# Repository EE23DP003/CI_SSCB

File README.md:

# CI_SSCB
This repository contains design files for two different coupled inductor based Solid-State Circuit Breakers (SSCBs)

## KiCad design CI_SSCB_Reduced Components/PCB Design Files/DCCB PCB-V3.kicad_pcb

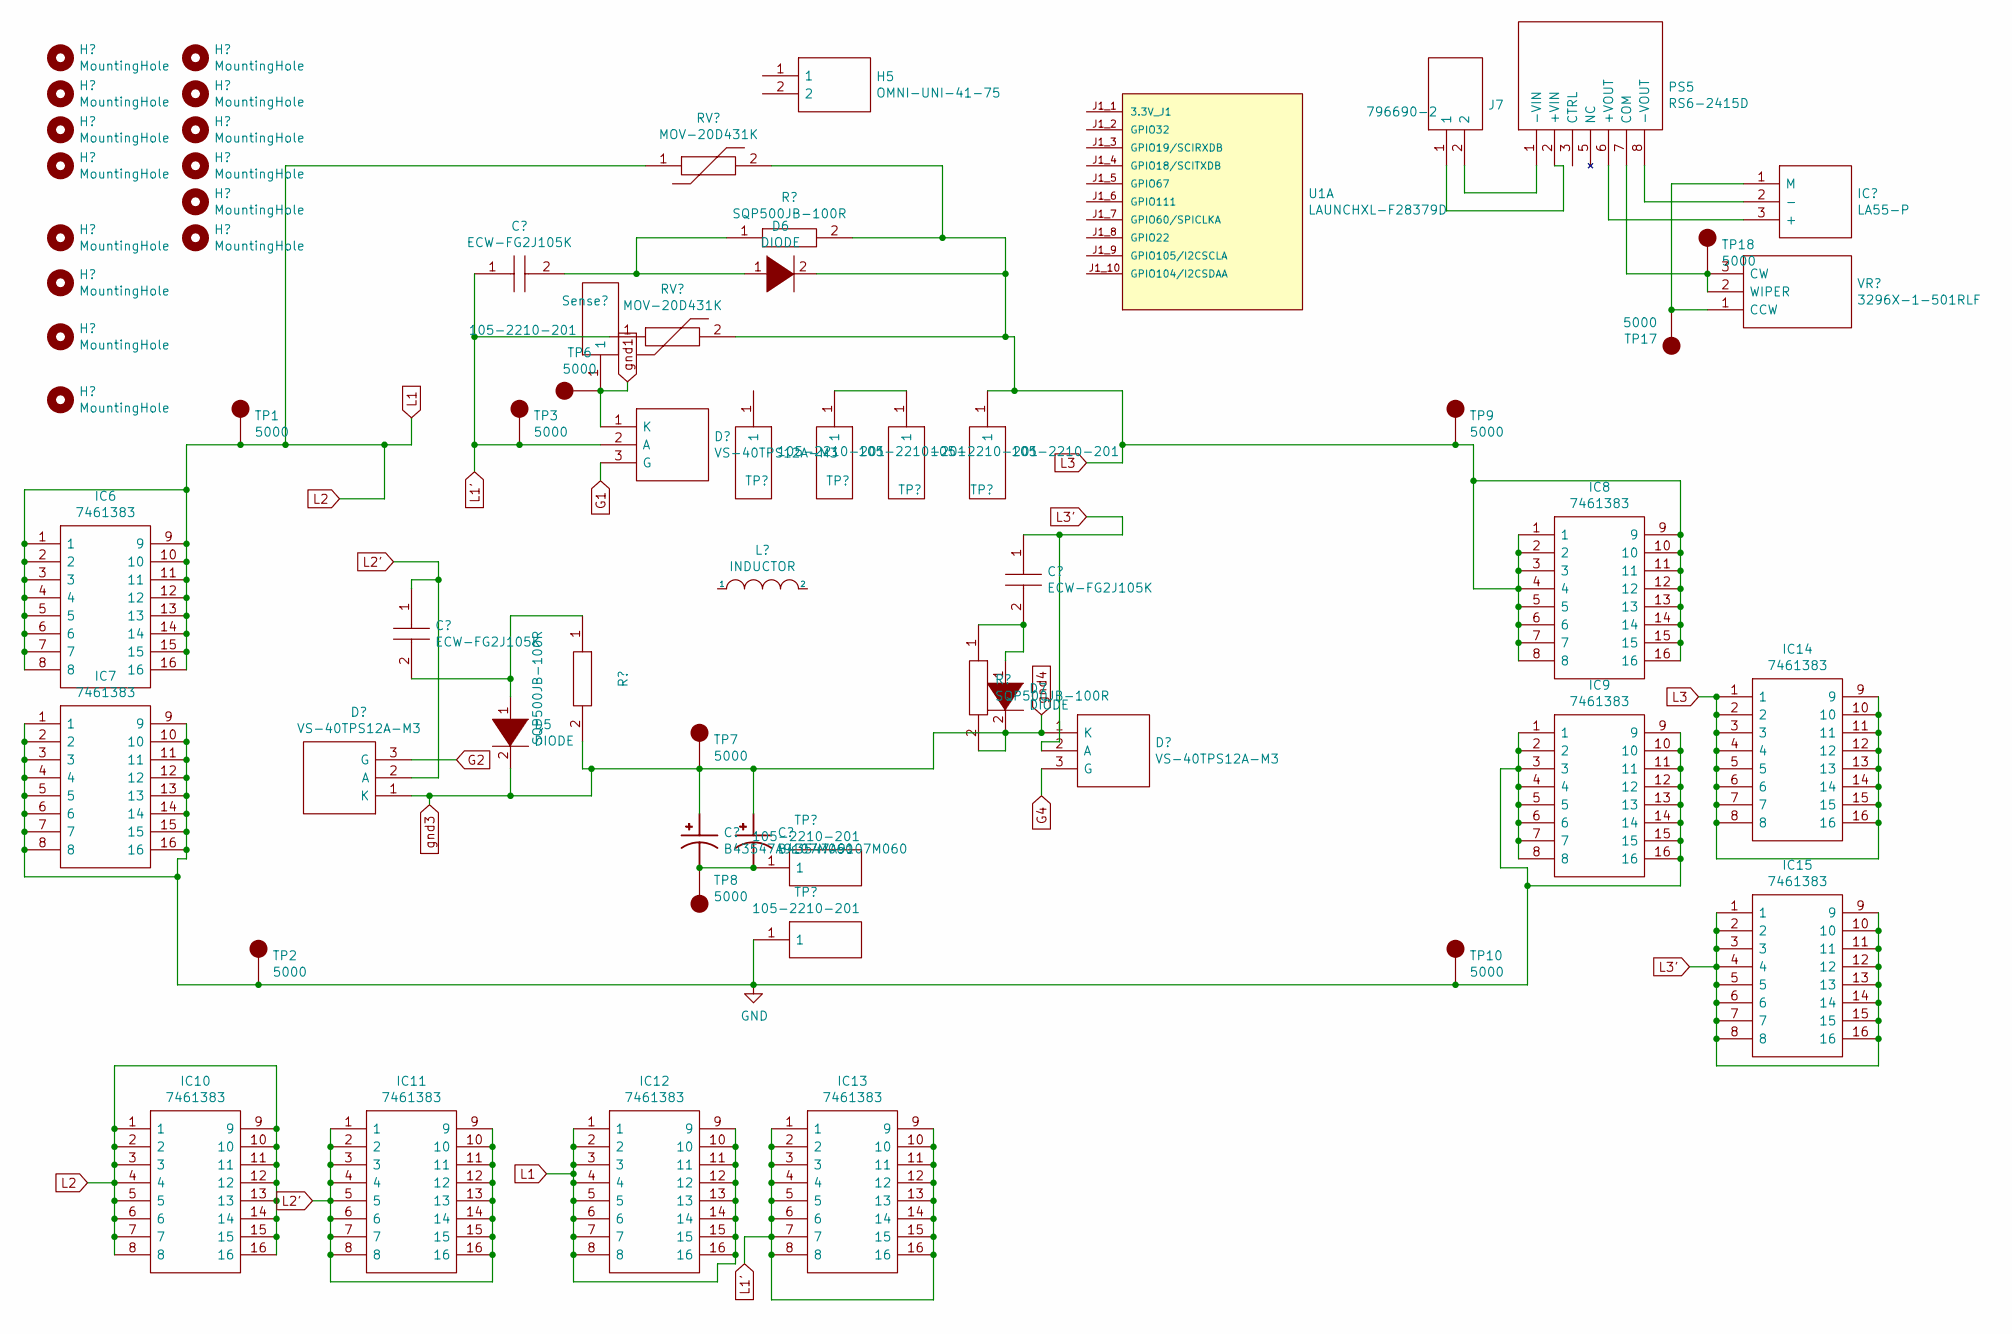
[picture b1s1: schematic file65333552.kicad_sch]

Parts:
C1, C2, C4: ECW-FG2J105K; ECWFG2J105K; Manufacturer_Part_Number ECW-FG2J105K
C3, C11: B43547A9107M060; CAPPRD1000W190D2550H2700; PARTREV 2018-10
D1, D2, D3: VS-40TPS12A-M3; TO546P531X1558X2499-3P; Manufacturer_Part_Number VS-40TPS12A-M3; Mouser Part Number 844-40TPS12A-M3
D5, D6, D7: DIODE; D_P600_R-6_P12.70mm_Horizontal
H1, H2, H3, H4, H6, H7, H8, H9, H10, H11, H12, H13, H14, H15: MountingHole; MountingHole_3.2mm_M3
H5: OMNI-UNI-41-75; OMNIUNI4175; Mouser Part Number 567-OMNI-UNI-41-75
IC1: LA55-P; LA55P; Manufacturer_Part_Number LA55-P
IC6, IC7, IC8, IC9, IC10, IC11, IC12, IC13, IC14, IC15: 7461383; Manufacturer_Part_Number 7461383
J7: 796690-2; SHDR2W101P0X500_1X2_1000X1250X1500P; Manufacturer_Part_Number 796690-2; Mouser Part Number 571-796690-2
K1: 105-2210-201; 1052210201; Mouser Part Number 530-105-2210-1
L1: INDUCTOR; EE422120_bobbin_diff_modified
PS5: RS6-2415D; RS60505S; Manufacturer_Part_Number RS6-2415D; Mouser Part Number 919-RS6-2415D
Probe1, Probe2: 105-2210-201; 1052210201; Mouser Part Number 530-105-2210-1
R1, R2, R3: SQP500JB-100R; RESAD6000W85L2200D950; Manufacturer_Part_Number SQP500JB-100R; Mouser Part Number 603-SQP500JB-100R
RV1, RV2: MOV-20D431K; MOV20D431K; Manufacturer_Part_Number MOV-20D431K; Mouser Part Number 652-MOV-20D431K
Sense1, Sense2: 105-2210-201; 1052210201; Mouser Part Number 530-105-2210-1
TP1, TP2, TP3, TP6, TP7, TP8, TP9, TP10, TP17, TP18: 5000; KEYSTONE_5000
TP4, TP5: 105-2210-201; 1052210201; Mouser Part Number 530-105-2210-1
U1: LAUNCHXL-F28379D; MOD_LAUNCHXL-F28379D; PARTREV 2.0
VR1: 3296X-1-501RLF; 3296X1223LF; Manufacturer_Part_Number 3296X-1-501RLF; Mouser Part Number 652-3296X-1-501RLF

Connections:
G1: D2.3 (G); also elsewhere on the board
G2: D1.3 (G); also elsewhere on the board
G4: D3.3 (G); also elsewhere on the board
GND: IC7.1, IC7.2, IC7.3, IC7.4, IC7.5, IC7.6, IC7.7, IC7.8, IC7.9, IC7.10, IC7.11, IC7.12, IC7.13, IC7.14, IC7.15, IC7.16, IC9.1, IC9.2, IC9.3, IC9.4, IC9.5, IC9.6, IC9.7, IC9.8, IC9.9, IC9.10, IC9.11, IC9.12, IC9.13, IC9.14, IC9.15, IC9.16, TP2.TP, TP5.1, TP10.TP
L1: IC6.1, IC6.2, IC6.3, IC6.4, IC6.5, IC6.6, IC6.7, IC6.8, IC6.9, IC6.10, IC6.11, IC6.12, IC6.13, IC6.14, IC6.15, IC6.16, IC10.1, IC10.2, IC10.3, IC10.4, IC10.5, IC10.6, IC10.7, IC10.8, IC10.9, IC10.10, IC10.11, IC10.12, IC10.13, IC10.14, IC10.15, IC10.16, IC12.1, IC12.2, IC12.3, IC12.4, IC12.5, IC12.6, IC12.7, IC12.8, IC12.9, IC12.10, IC12.11, IC12.12, IC12.13, IC12.14, IC12.15, IC12.16, RV2.1, TP1.TP
L1': C2.1, D2.2 (A), IC13.1, IC13.2, IC13.3, IC13.4, IC13.5, IC13.6, IC13.7, IC13.8, IC13.9, IC13.10, IC13.11, IC13.12, IC13.13, IC13.14, IC13.15, IC13.16, RV1.1, TP3.TP
L2': C1.1, D1.2 (A), IC11.1, IC11.2, IC11.3, IC11.4, IC11.5, IC11.6, IC11.7, IC11.8, IC11.9, IC11.10, IC11.11, IC11.12, IC11.13, IC11.14, IC11.15, IC11.16
L3: D6.2 (A), IC8.1, IC8.2, IC8.3, IC8.4, IC8.5, IC8.6, IC8.7, IC8.8, IC8.9, IC8.10, IC8.11, IC8.12, IC8.13, IC8.14, IC8.15, IC8.16, IC14.1, IC14.2, IC14.3, IC14.4, IC14.5, IC14.6, IC14.7, IC14.8, IC14.9, IC14.10, IC14.11, IC14.12, IC14.13, IC14.14, IC14.15, IC14.16, Probe2.1, R2.2, RV1.2, RV2.2, TP9.TP
L3': C4.1, D3.2 (A), IC15.1, IC15.2, IC15.3, IC15.4, IC15.5, IC15.6, IC15.7, IC15.8, IC15.9, IC15.10, IC15.11, IC15.12, IC15.13, IC15.14, IC15.15, IC15.16
unnamed: C1.2, D5.1 (K), R1.1
unnamed: C2.2, D6.1 (K), R2.1
unnamed: C4.2, D7.1 (K), R3.1
unnamed: C3.2, C11.2, TP4.1, TP8.TP
unnamed: IC1.1 (M), TP17.TP, VR1.1 (CCW)
unnamed: IC1.2 (-), PS5.8 (-VOUT)
unnamed: IC1.3 (+), PS5.6 (+VOUT)
unnamed: J7.1, PS5.2 (+VIN)
unnamed: J7.2, PS5.1 (-VIN)
unnamed: PS5.7 (COM), TP18.TP, VR1.2 (WIPER), VR1.3 (CW)
unnamed: Probe1.1, Sense2.1
gnd1: D2.1 (K), K1.1, TP6.TP; also elsewhere on the board
gnd3: C3.1, C11.1, D1.1 (K), D3.1 (K), D5.2 (A), D7.2 (A), R1.2, R3.2, TP7.TP; also elsewhere on the board

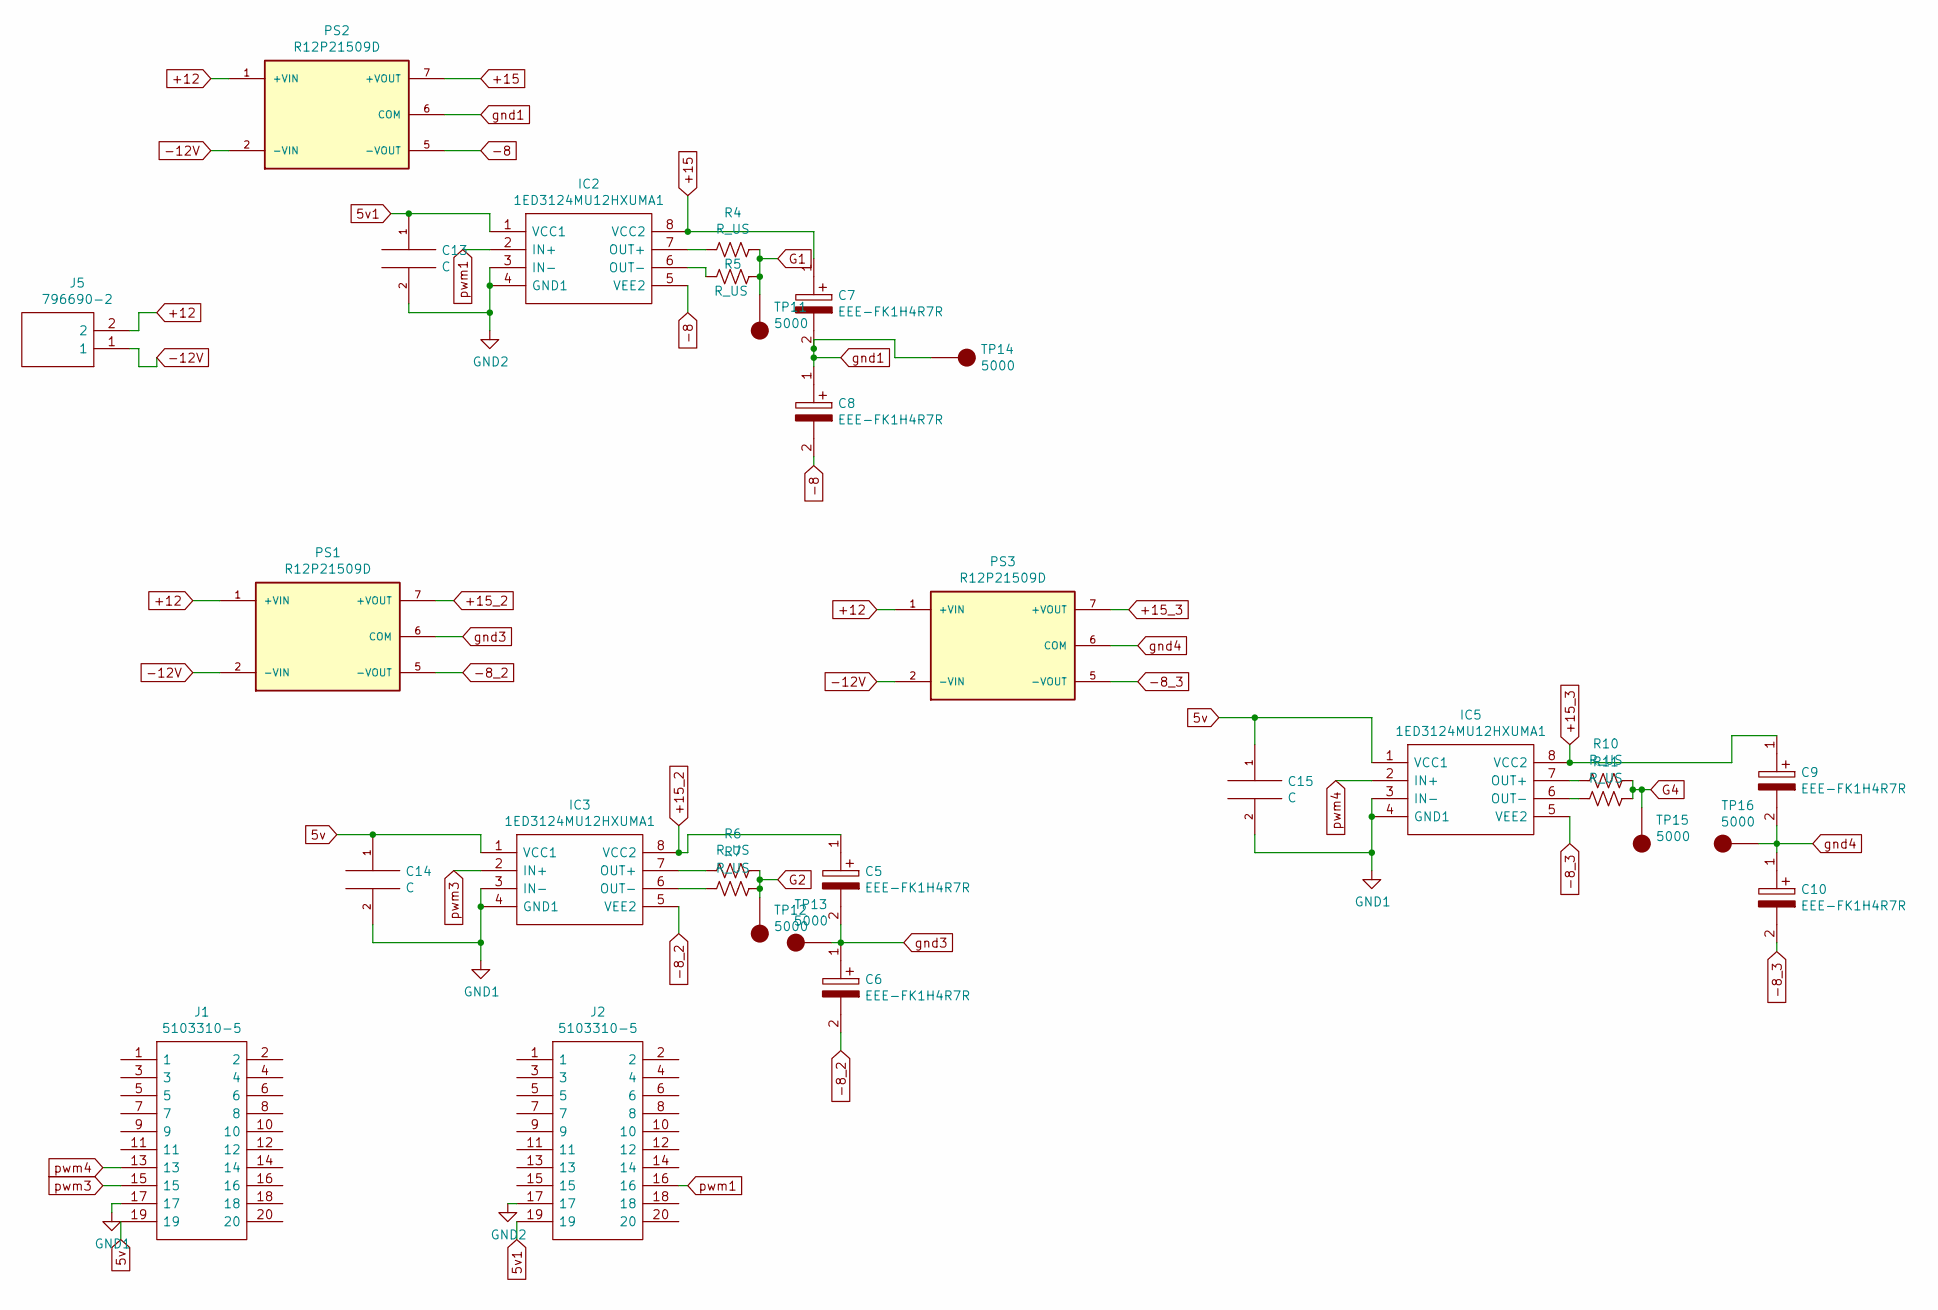
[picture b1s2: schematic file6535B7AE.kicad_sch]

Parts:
C5, C6, C7, C8, C9, C10: EEE-FK1H4R7R; EEE1AA220WR; Mouser Part Number 667-EEE-FK1H4R7R
C13, C14, C15: C; C_0603_1608Metric_Pad1.08x0.95mm_HandSolder
IC2, IC3, IC5: 1ED3124MU12HXUMA1; SOIC127P1030X265-8N; Mouser Part Number 726-1ED3124MU12HXUMA
J1, J2: 5103310-5; SHDRRA20W66P254_2X10_3289X986X927P; Manufacturer_Part_Number 5103310-5
J5: 796690-2; SHDR2W101P0X500_1X2_1000X1250X1500P; Manufacturer_Part_Number 796690-2; Mouser Part Number 571-796690-2
PS1, PS2, PS3: R12P21509D; CONV_R12P21509D; PARTREV 5
R4, R5, R6, R7, R10, R11: R_US; R_0603_1608Metric_Pad0.98x0.95mm_HandSolder
TP11, TP12, TP13, TP14, TP15, TP16: 5000; KEYSTONE_5000

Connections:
5v: C14.1, C15.1, IC3.1 (VCC1), IC5.1 (VCC1), J1.19
5v1: C13.1, IC2.1 (VCC1), J2.19
+12: J5.2, PS1.1 (+VIN), PS2.1 (+VIN), PS3.1 (+VIN)
+15: C7.1, IC2.8 (VCC2), PS2.7 (+VOUT)
+15_2: C5.1, IC3.8 (VCC2), PS1.7 (+VOUT)
+15_3: C9.1, IC5.8 (VCC2), PS3.7 (+VOUT)
-8: C8.2, IC2.5 (VEE2), PS2.5 (-VOUT)
-8_2: C6.2, IC3.5 (VEE2), PS1.5 (-VOUT)
-8_3: C10.2, IC5.5 (VEE2), PS3.5 (-VOUT)
-12V: J5.1, PS1.2 (-VIN), PS2.2 (-VIN), PS3.2 (-VIN)
G1: R4.1, R5.1, TP11.TP; also elsewhere on the board
G2: R6.1, R7.1, TP12.TP; also elsewhere on the board
G4: R10.1, R11.1, TP15.TP; also elsewhere on the board
GND1: C14.2, C15.2, IC3.3 (IN-), IC3.4 (GND1), IC5.3 (IN-), IC5.4 (GND1), J1.17
GND2: C13.2, IC2.3 (IN-), IC2.4 (GND1), J2.17
unnamed: IC2.6 (OUT-), R5.2
unnamed: IC2.7 (OUT+), R4.2
unnamed: IC3.6 (OUT-), R7.2
unnamed: IC3.7 (OUT+), R6.2
unnamed: IC5.6 (OUT-), R11.2
unnamed: IC5.7 (OUT+), R10.2
gnd1: C7.2, C8.1, PS2.6 (COM), TP14.TP; also elsewhere on the board
gnd3: C5.2, C6.1, C9.2, C10.1, PS1.6 (COM), PS3.6 (COM), TP13.TP, TP16.TP; also elsewhere on the board
pwm1: IC2.2 (IN+), J2.16
pwm3: IC3.2 (IN+), J1.15
pwm4: IC5.2 (IN+), J1.13

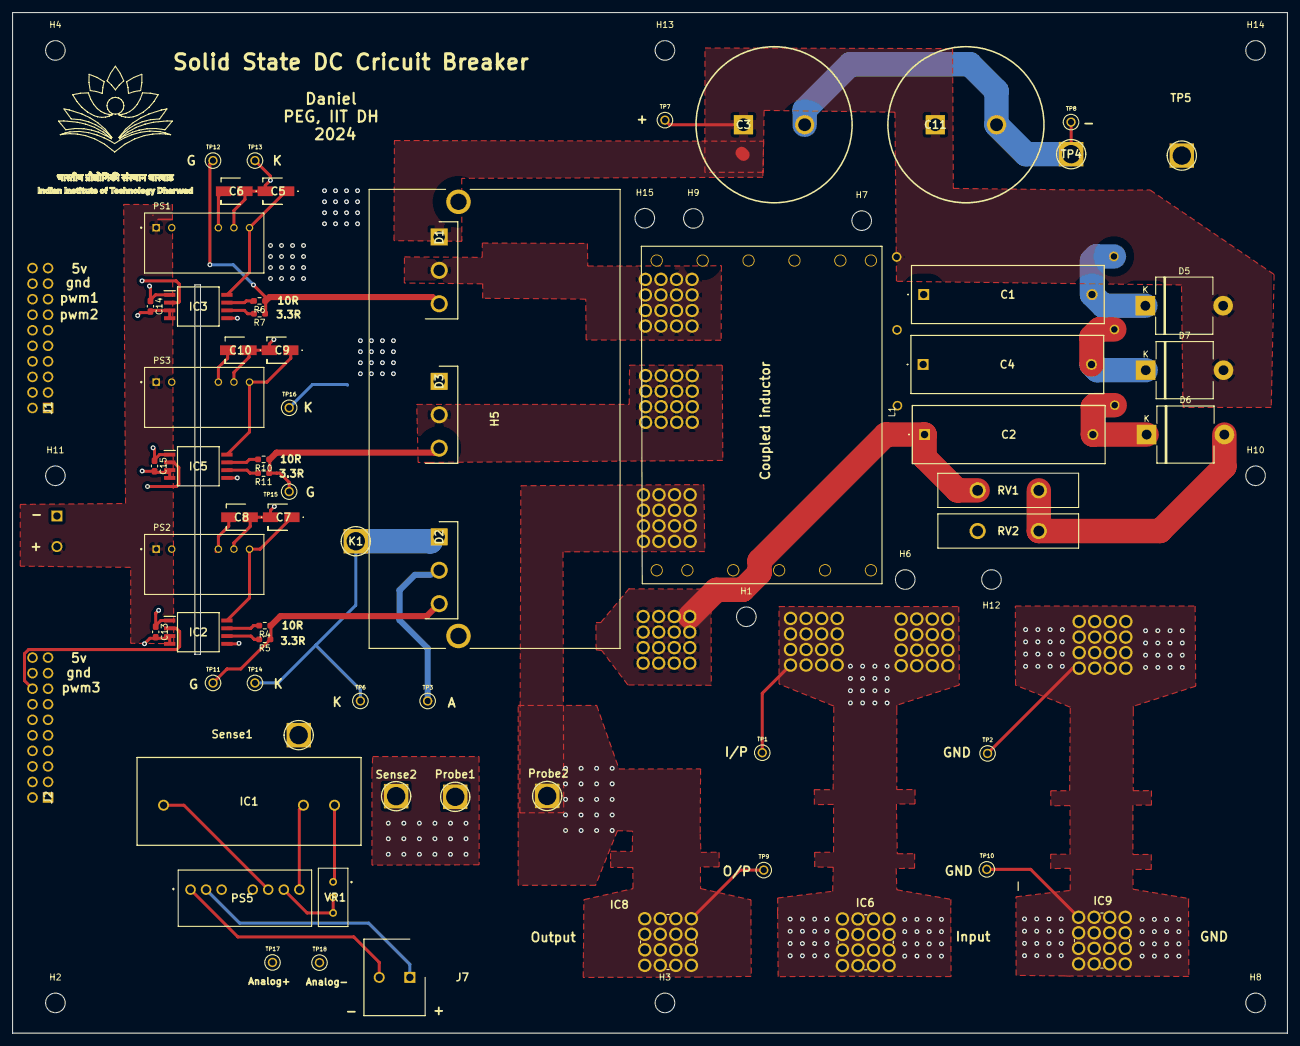
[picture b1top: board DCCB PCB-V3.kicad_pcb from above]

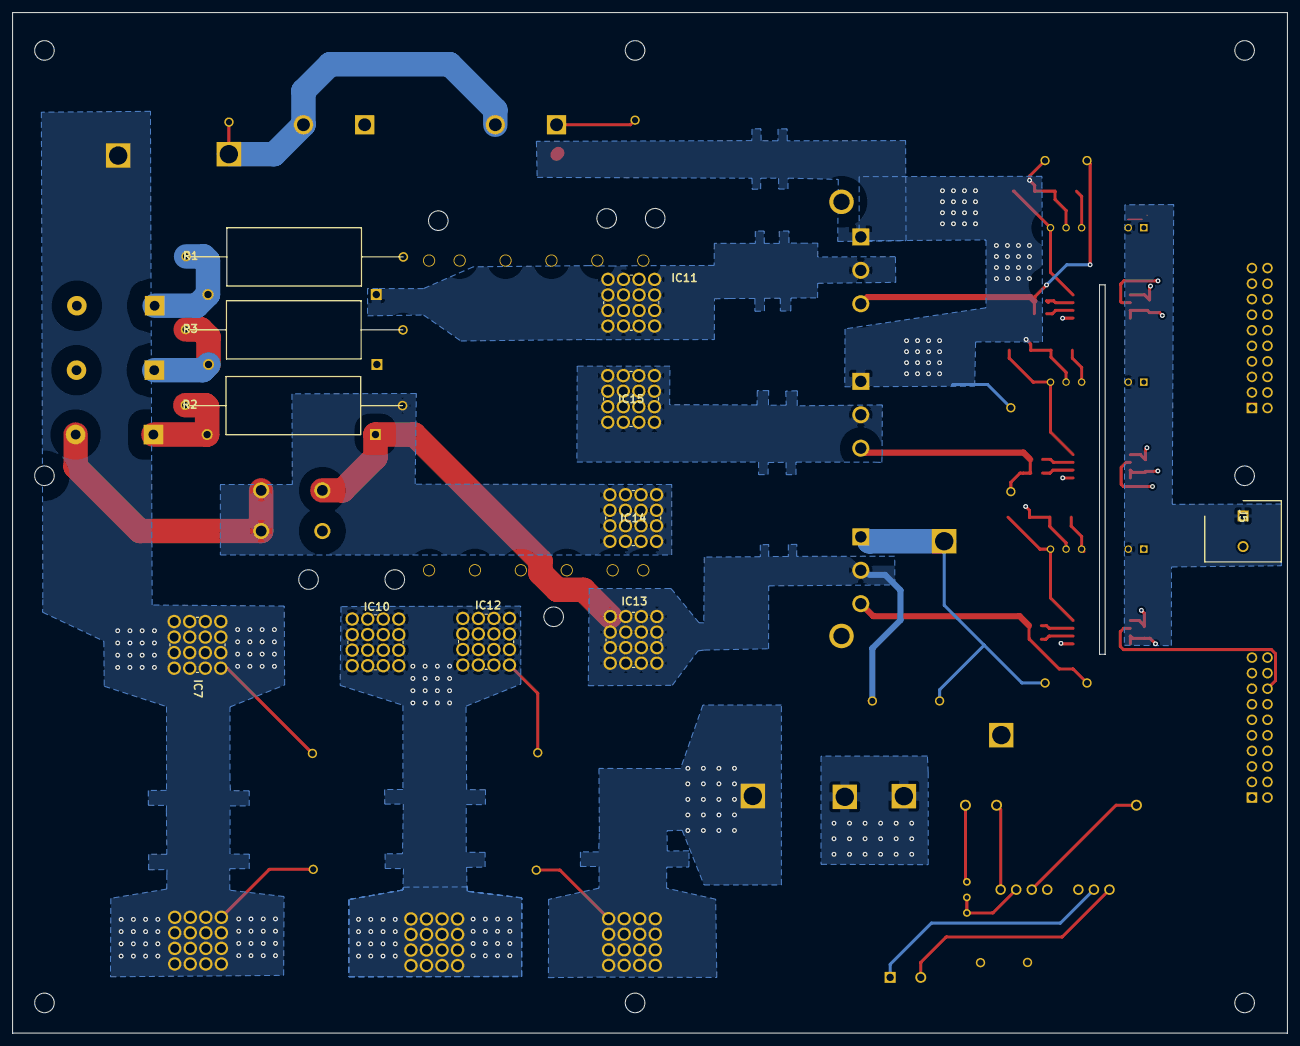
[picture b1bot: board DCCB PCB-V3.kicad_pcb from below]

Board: 4 copper layers, 208.3 x 166.7 mm, 94 parts (11 on the bottom side), 43 nets.

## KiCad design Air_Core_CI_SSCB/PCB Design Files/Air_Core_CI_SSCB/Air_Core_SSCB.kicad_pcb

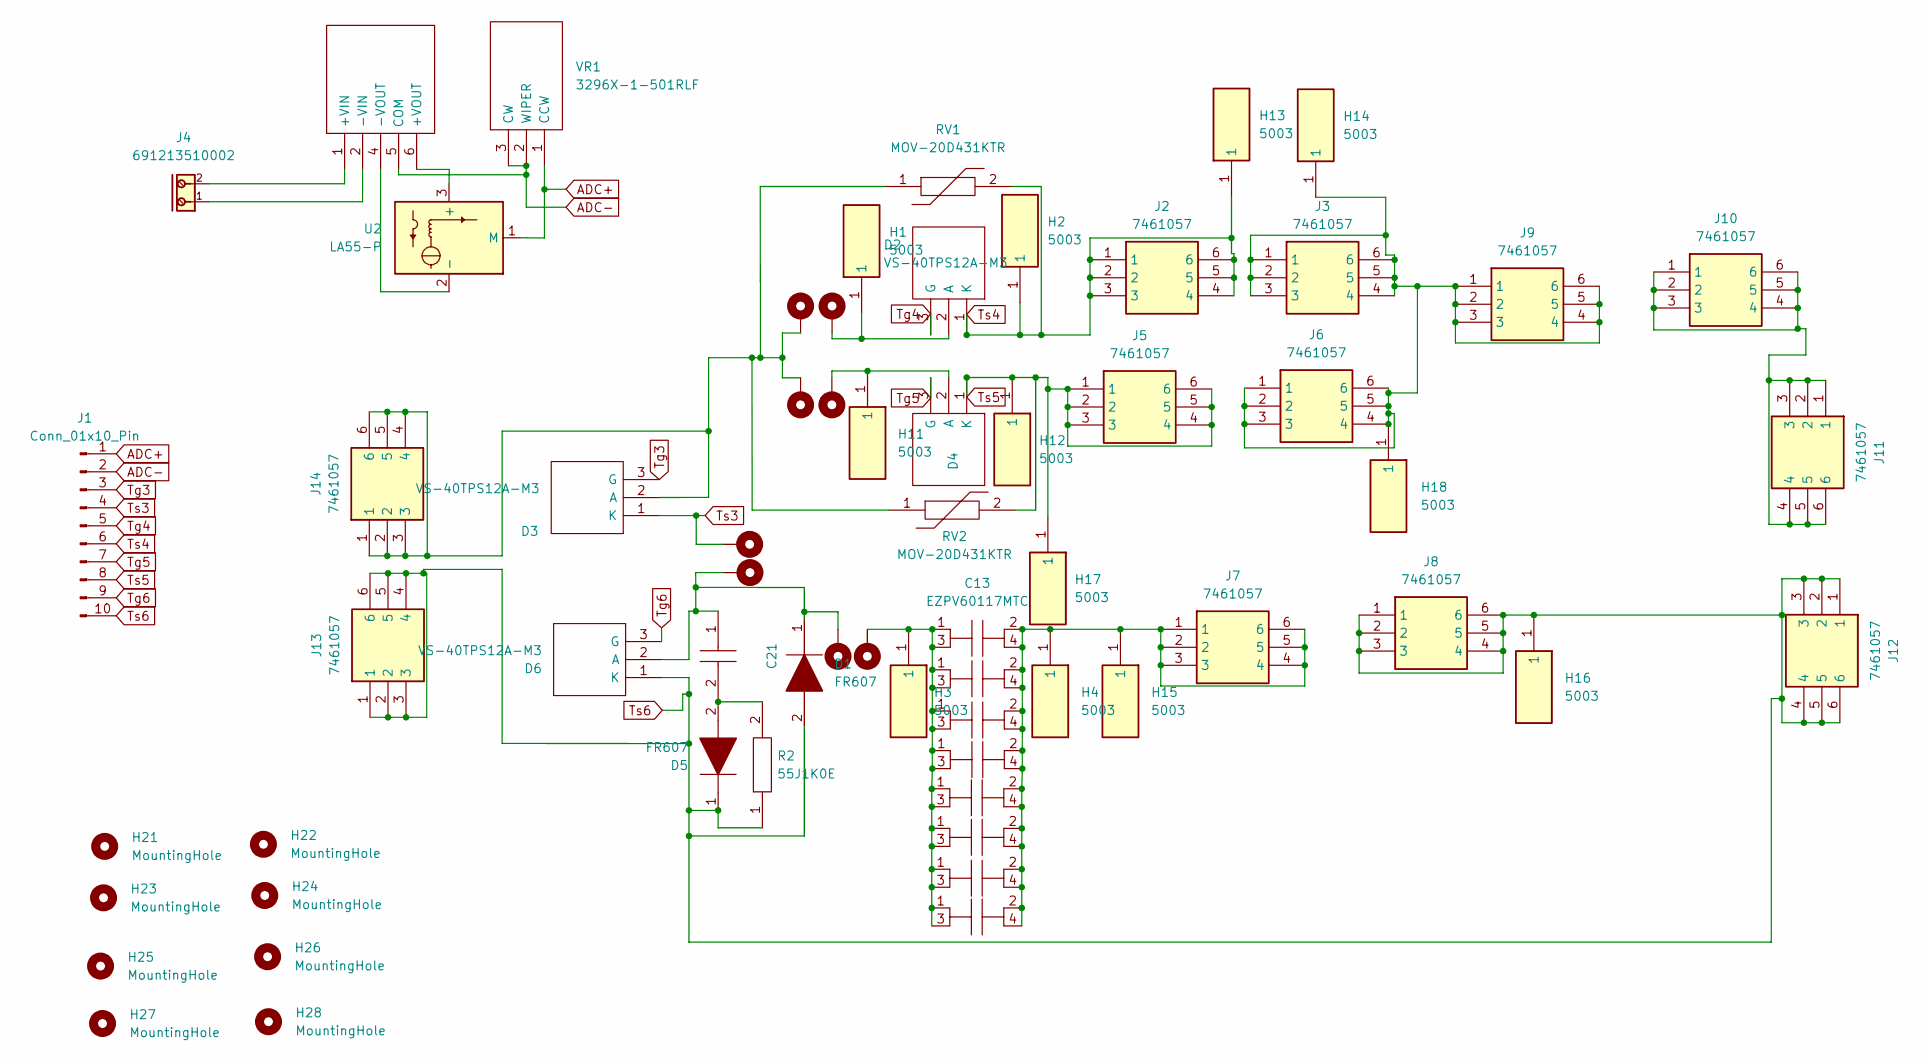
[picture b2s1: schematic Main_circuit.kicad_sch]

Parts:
C1, C13, C14, C15, C16, C17, C18, C19: EZPV60117MTC; Manufacturer_Part_Number EZPV60117MTC
C21: ECWFG2J105K; Manufacturer_Part_Number ECWFG2J105K
D1, D5: FR607; D_P600_R-6_P12.70mm_Horizontal; Manufacturer_Part_Number FR607
D2, D3, D4, D6: VS-40TPS12A-M3; TO546P531X1558X2499-3P; Manufacturer_Part_Number VS-40TPS12A-M3
H1, H2, H3, H4, H11, H12, H13, H14, H15, H16, H17, H18: 5003; Manufacturer_Part_Number 5003
H5, H6, H7, H8, H9, H10, H19, H20: MountingHole_Pad; MountingHole_2.2mm_M2_ISO7380_Pad
H21, H22, H23, H24, H25, H26, H27, H28: MountingHole; MountingHole_3.2mm_M3
J1: Conn_01x10_Pin; PinSocket_1x10_P2.54mm_Vertical
J2, J3, J5, J6, J7, J8, J9, J10, J11, J12, J13, J14: 7461057; Manufacturer_Part_Number 7461057
J4: 691213510002; PART-NUMBER 691213510002
R2: 55J1K0E; RESAD5300W105L2100D800; Manufacturer_Part_Number 55J1K0E; Mouser Part Number 588-55J1K0E
RV1, RV2: MOV-20D431KTR; MOV20D431K; Mouser Part Number 652-MOV-20D431KTR
U1: RB-1215D_HP; RB1215DHP; Manufacturer_Part_Number RB-1215D/HP; Mouser Part Number 919-RB-1215D/HP
U2: LA55-P
VR1: 3296X-1-501RLF; 3296X1223LF; Manufacturer_Part_Number 3296X-1-501RLF; Mouser Part Number 652-3296X-1-501RLF

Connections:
ADC+: J1.1, U2.1 (M), VR1.1 (CCW)
ADC-: J1.2, U1.5 (COM), VR1.2 (WIPER), VR1.3 (CW)
unnamed: C1.1, C1.3, C13.1, C13.3, C14.1, C14.3, C15.1, C15.3, C16.1, C16.3, C17.1, C17.3, C18.1, C18.3, C19.1, C19.3, H3.1, H6.1
unnamed: C1.2, C1.4, C13.2, C13.4, C14.2, C14.4, C15.2, C15.4, C16.2, C16.4, C17.2, C17.4, C18.2, C18.4, C19.2, C19.4, H4.1, H15.1, J7.1, J7.2, J7.3, J7.4, J7.5, J7.6
unnamed: C21.2, D5.2, R2.2
unnamed: D2.2 (A), H1.1, H10.1
unnamed: D3.2 (A), H7.1, H9.1, J14.1, J14.2, J14.3, J14.4, J14.5, J14.6, RV1.1, RV2.1
unnamed: D4.2 (A), H8.1, H11.1
unnamed: C21.1, D1.1, D6.2 (A), H5.1, H19.1
unnamed: H14.1, H18.1, J3.1, J3.2, J3.3, J3.4, J3.5, J3.6, J6.1, J6.2, J6.3, J6.4, J6.5, J6.6, J9.1, J9.2, J9.3, J9.4, J9.5, J9.6
unnamed: J10.1, J10.2, J10.3, J10.4, J10.5, J10.6, J11.1, J11.2, J11.3, J11.4, J11.5, J11.6
unnamed: J4.2, U1.1 (+VIN)
unnamed: U1.6 (+VOUT), U2.3 (+)
unnamed: J4.1, U1.2 (-VIN)
unnamed: U1.4 (-VOUT), U2.2 (-)
Tg3: D3.3 (G), J1.3
Tg4: D2.3 (G), J1.5
Tg5: D4.3 (G), J1.7
Tg6: D6.3 (G), J1.9
Ts3: D3.1 (K), H20.1, J1.4
Ts4: D2.1 (K), H2.1, H13.1, J1.6, J2.1, J2.2, J2.3, J2.4, J2.5, J2.6, RV1.2
Ts5: D4.1 (K), H12.1, H17.1, J1.8, J5.1, J5.2, J5.3, J5.4, J5.5, J5.6, RV2.2
Ts6: D1.2, D5.1, D6.1 (K), H16.1, J1.10, J8.1, J8.2, J8.3, J8.4, J8.5, J8.6, J12.1, J12.2, J12.3, J12.4, J12.5, J12.6, J13.1, J13.2, J13.3, J13.4, J13.5, J13.6, R2.1

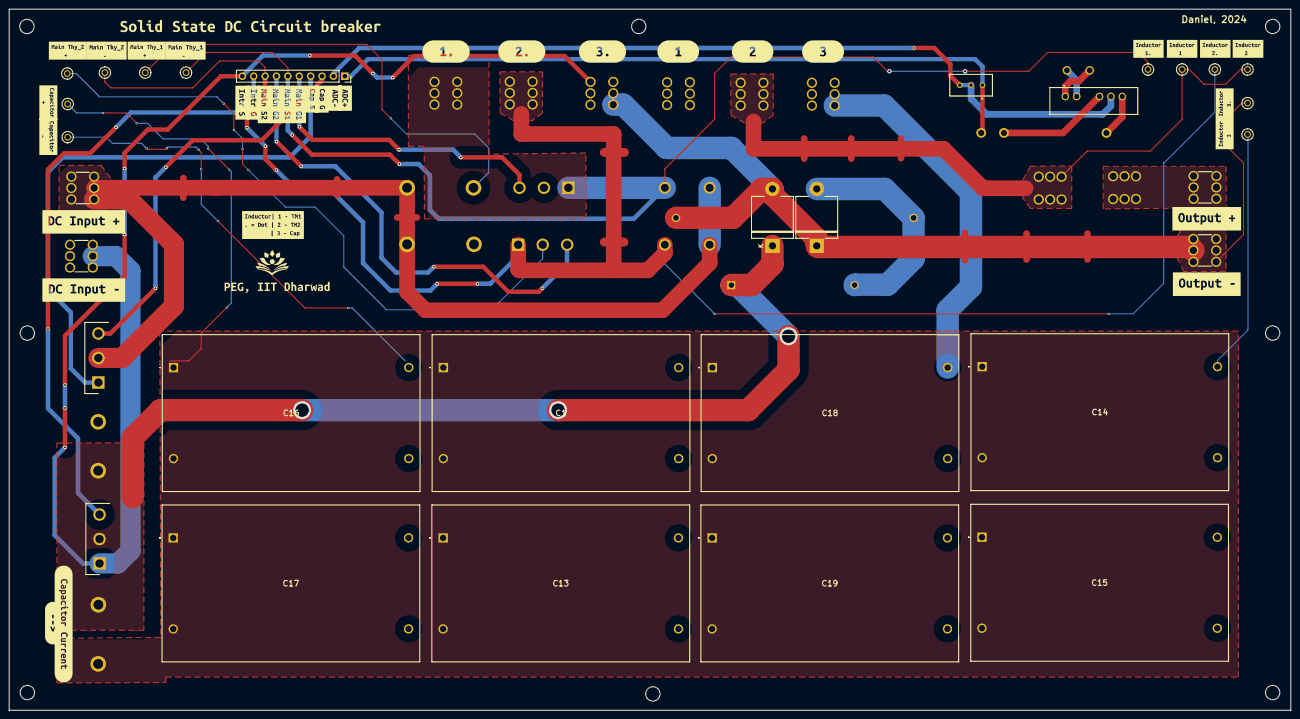
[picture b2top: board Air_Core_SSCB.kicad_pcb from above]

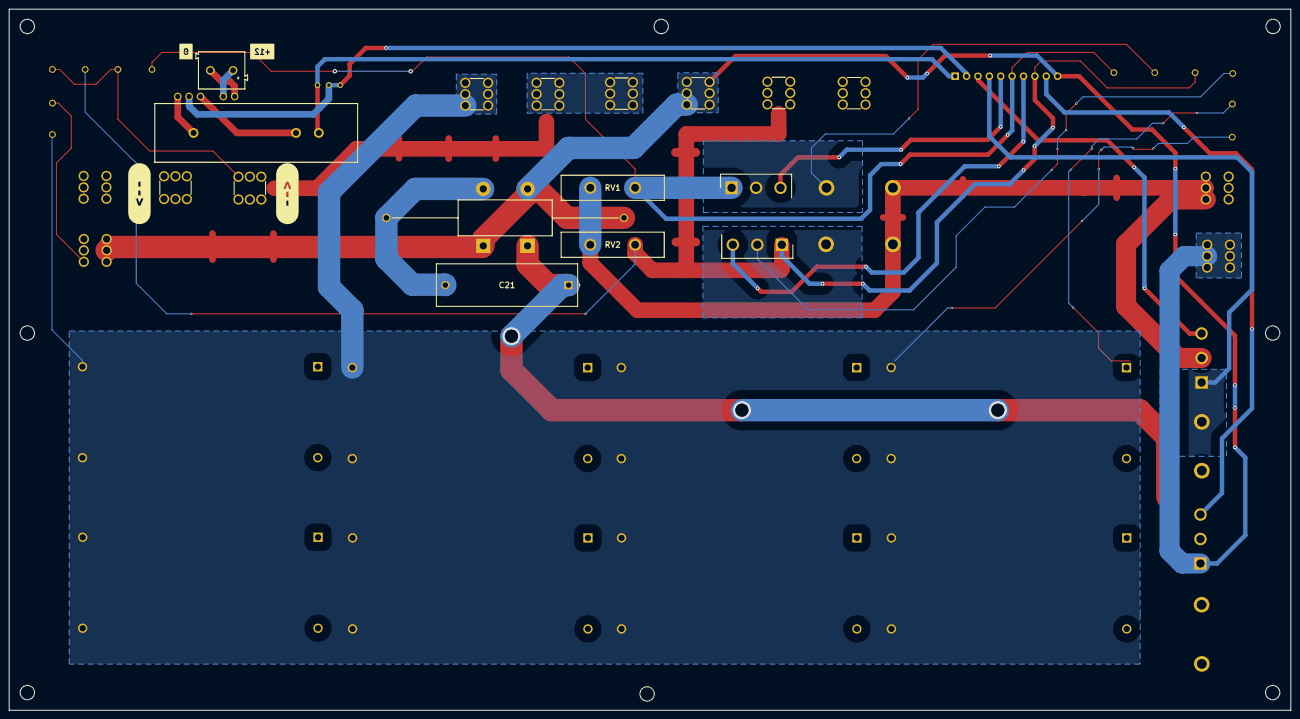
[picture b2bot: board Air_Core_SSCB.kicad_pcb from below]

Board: 2 copper layers, 285.9 x 156.4 mm, 104 parts (16 on the bottom side), 23 nets.

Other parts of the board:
kibuzzard-65DB8DD2: G***; kibuzzard-65DB8DD2
kibuzzard-65DB8FAA: G***; kibuzzard-65DB8FAA
kibuzzard-65DB9A7A: G***; kibuzzard-65DB9A7A
kibuzzard-65DB9A19: G***; kibuzzard-65DB9A19
kibuzzard-65DB9A81: G***; kibuzzard-65DB9A81
kibuzzard-65DB9A89: G***; kibuzzard-65DB9A89
kibuzzard-65DB9ACE: G***; kibuzzard-65DB9ACE
kibuzzard-65DB9ADC: G***; kibuzzard-65DB9ADC
kibuzzard-65DB9B86: G***; kibuzzard-65DB9B86
kibuzzard-65DB9BA2: G***; kibuzzard-65DB9BA2
kibuzzard-65DB99B3: G***; kibuzzard-65DB99B3
kibuzzard-65DB885A: G***; kibuzzard-65DB885A
kibuzzard-65DB886D: G***; kibuzzard-65DB886D
kibuzzard-65DB887A: G***; kibuzzard-65DB887A
kibuzzard-65DB8860: G***; kibuzzard-65DB8860
kibuzzard-65DB8867: G***; kibuzzard-65DB8867
kibuzzard-65DB8874: G***; kibuzzard-65DB8874
kibuzzard-65EAEA41: G***; kibuzzard-65EAEA41
kibuzzard-66224FE1: G***; kibuzzard-66224FE1
kibuzzard-66224FFF: G***; kibuzzard-66224FFF
kibuzzard-66225C22, kibuzzard-66225C22#2: G***; kibuzzard-66225C22
kibuzzard-66225CC6: G***; kibuzzard-66225CC6
kibuzzard-66225D99: G***; kibuzzard-66225D99
kibuzzard-66225F03: G***; kibuzzard-66225F03
kibuzzard-66239A2E: G***; kibuzzard-66239A2E
kibuzzard-662260A2: G***; kibuzzard-662260A2
kibuzzard-662260AF: G***; kibuzzard-662260AF
kibuzzard-662260ED: G***; kibuzzard-662260ED
kibuzzard-662260F8: G***; kibuzzard-662260F8
kibuzzard-662392F0: G***; kibuzzard-662392F0
kibuzzard-6622505D: G***; kibuzzard-6622505D
kibuzzard-6622506C: G***; kibuzzard-6622506C
kibuzzard-6622609D: G***; kibuzzard-6622609D
kibuzzard-6622622D: G***; kibuzzard-6622622D
kibuzzard-6622636A: G***; kibuzzard-6622636A
kibuzzard-6622637B: G***; kibuzzard-6622637B
kibuzzard-66226075: G***; kibuzzard-66226075
kibuzzard-66226237: G***; kibuzzard-66226237
kibuzzard-66226323: G***; kibuzzard-66226323
kibuzzard-66226341: G***; kibuzzard-66226341

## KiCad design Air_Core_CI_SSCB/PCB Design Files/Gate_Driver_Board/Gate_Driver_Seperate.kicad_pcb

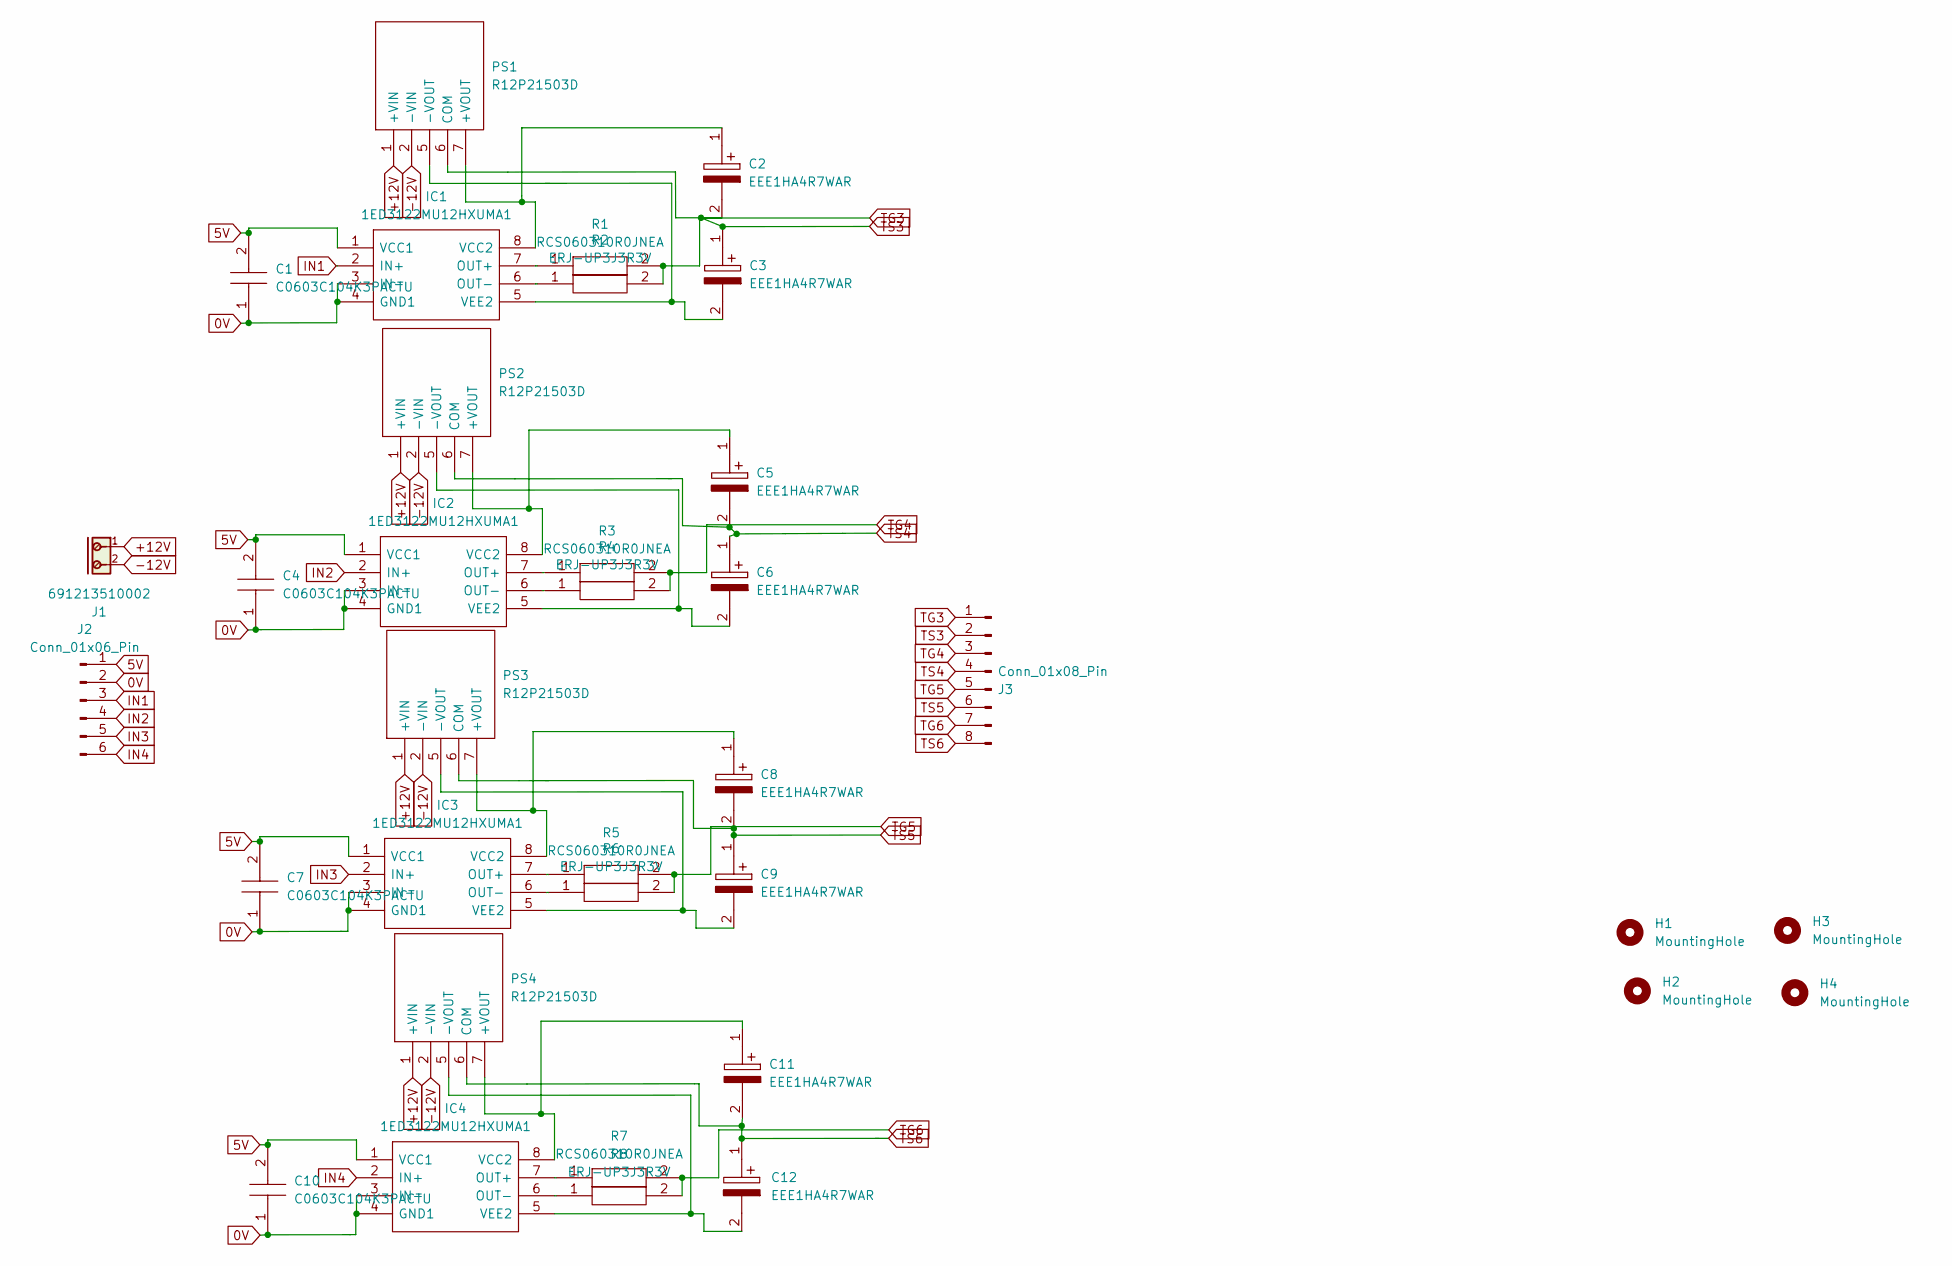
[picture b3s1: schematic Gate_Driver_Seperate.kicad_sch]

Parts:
C1, C4, C7, C10: C0603C104K3PACTU; C0603; Manufacturer_Part_Number C0603C104K3PACTU
C2, C3, C5, C6, C8, C9, C11, C12: EEE1HA4R7WAR; EEE1AA220WR; Manufacturer_Part_Number EEE1HA4R7WAR
H1, H2, H3, H4: MountingHole; MountingHole_3.2mm_M3
IC1, IC2, IC3, IC4: 1ED3122MU12HXUMA1; SOIC127P1030X265-8N; Manufacturer_Part_Number 1ED3122MU12HXUMA1
J1: 691213510002; PART-NUMBER 691213510002
J2: Conn_01x06_Pin; PinHeader_1x06_P2.54mm_Vertical
J3: Conn_01x08_Pin; PinHeader_1x08_P2.54mm_Vertical
PS1, PS2, PS3, PS4: R12P21503D; Manufacturer_Part_Number R12P21503D
R1, R3, R5, R7: RCS060310R0JNEA; RCS0603_E3; Manufacturer_Part_Number RCS060310R0JNEA
R2, R4, R6, R8: ERJ-UP3J3R3V; ERJUP3; Manufacturer_Part_Number ERJ-UP3J3R3V

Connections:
0V: C1.1, C4.1, C7.1, C10.1, IC1.3 (IN-), IC1.4 (GND1), IC2.3 (IN-), IC2.4 (GND1), IC3.3 (IN-), IC3.4 (GND1), IC4.3 (IN-), IC4.4 (GND1), J2.2
5V: C1.2, C4.2, C7.2, C10.2, IC1.1 (VCC1), IC2.1 (VCC1), IC3.1 (VCC1), IC4.1 (VCC1), J2.1
+12V: J1.1, PS1.1 (+VIN), PS2.1 (+VIN), PS3.1 (+VIN), PS4.1 (+VIN)
-12V: J1.2, PS1.2 (-VIN), PS2.2 (-VIN), PS3.2 (-VIN), PS4.2 (-VIN)
IN1: IC1.2 (IN+), J2.3
IN2: IC2.2 (IN+), J2.4
IN3: IC3.2 (IN+), J2.5
IN4: IC4.2 (IN+), J2.6
unnamed: IC1.7 (OUT+), R1.1
unnamed: IC1.6 (OUT-), R2.1
unnamed: C2.1, IC1.8 (VCC2), PS1.7 (+VOUT)
unnamed: C3.2, IC1.5 (VEE2), PS1.5 (-VOUT)
unnamed: IC2.7 (OUT+), R3.1
unnamed: IC2.6 (OUT-), R4.1
unnamed: C5.1, IC2.8 (VCC2), PS2.7 (+VOUT)
unnamed: C6.2, IC2.5 (VEE2), PS2.5 (-VOUT)
unnamed: IC3.7 (OUT+), R5.1
unnamed: IC3.6 (OUT-), R6.1
unnamed: C8.1, IC3.8 (VCC2), PS3.7 (+VOUT)
unnamed: C9.2, IC3.5 (VEE2), PS3.5 (-VOUT)
unnamed: IC4.7 (OUT+), R7.1
unnamed: IC4.6 (OUT-), R8.1
unnamed: C11.1, IC4.8 (VCC2), PS4.7 (+VOUT)
unnamed: C12.2, IC4.5 (VEE2), PS4.5 (-VOUT)
TG3: J3.1, R1.2, R2.2
TG4: J3.3, R3.2, R4.2
TG5: J3.5, R5.2, R6.2
TG6: J3.7, R7.2, R8.2
TS3: C2.2, C3.1, J3.2, PS1.6 (COM)
TS4: C5.2, C6.1, J3.4, PS2.6 (COM)
TS5: C8.2, C9.1, J3.6, PS3.6 (COM)
TS6: C11.2, C12.1, J3.8, PS4.6 (COM)
